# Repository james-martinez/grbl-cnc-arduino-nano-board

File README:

Made with Eagle 6.1

A milled board
[[gollum.png|frame|alt=Gollum and his precious wiki]]

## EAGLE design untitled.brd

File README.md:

A PCB layout and schematic.

Made with Eagle PCB 6.1

##Requirements
* an arduino nano w atmega328p loaded with grbl http://github.com/grbl/grbl
* at least 1 Pololu A4988 Stepper motor driver

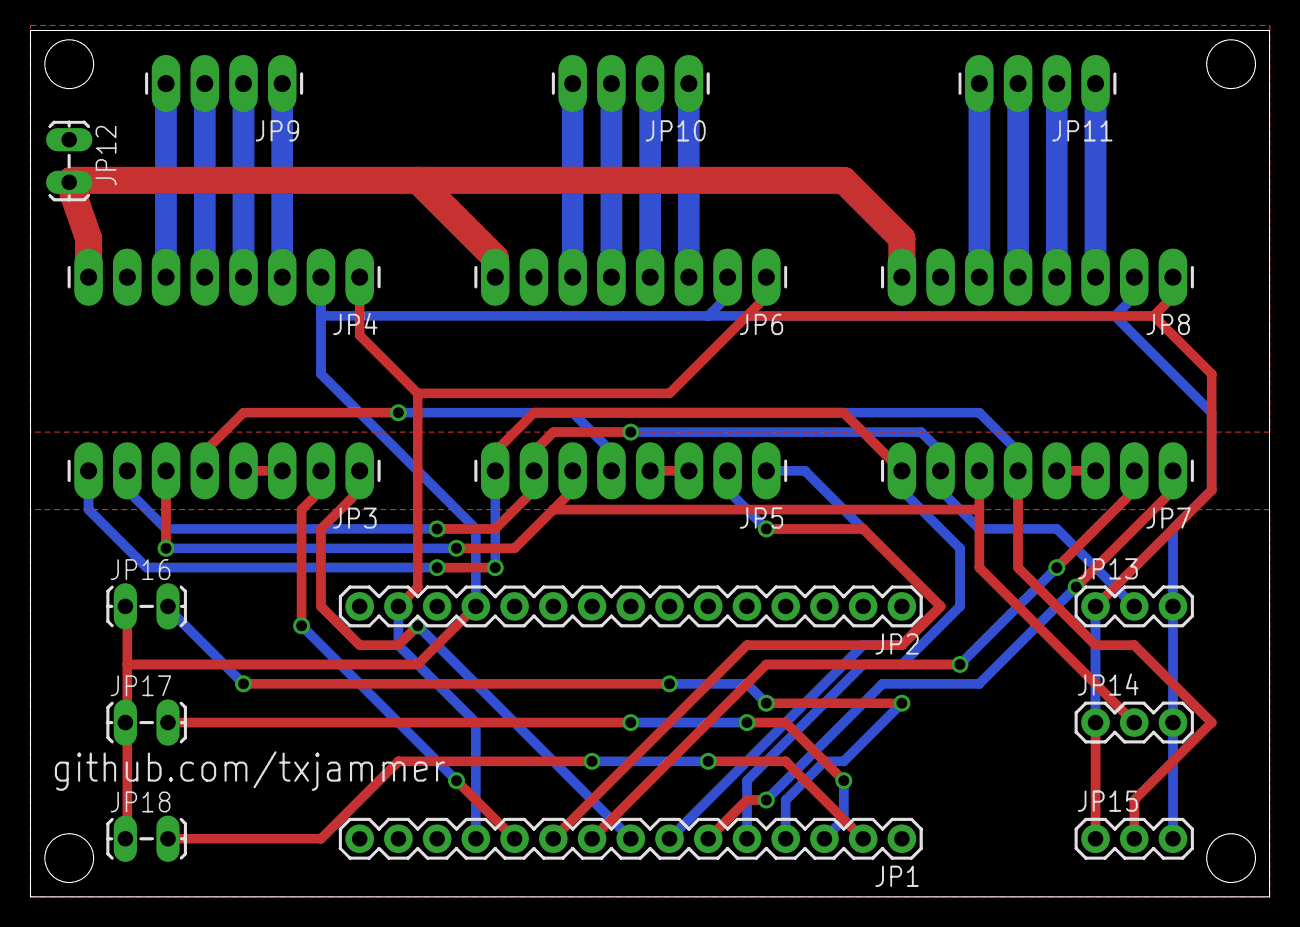
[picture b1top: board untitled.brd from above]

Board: 2 copper layers, 81.3 x 56.8 mm, 18 parts (0 on the bottom side), 32 nets.

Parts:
JP1, JP2: M15; 1X15
JP3, JP4, JP5, JP6, JP7, JP8: 1X08_LONGPADS
JP9, JP10, JP11: 1X04_LONGPADS
JP12, JP16, JP17, JP18: 1X02_LOCK_LONGPADS
JP13, JP14, JP15: 1X03

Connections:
5V: JP2.12, JP4.2, JP6.2, JP8.2, JP13.3, JP14.3, JP15.3, JP16.1, JP17.1, JP18.1
DISABLE: JP1.5, JP3.8, JP5.8, JP7.8
GND: JP1.12, JP2.14, JP4.1, JP6.1, JP8.1, JP13.1, JP14.1, JP15.1
GNDMOT: JP4.7, JP6.7, JP8.7, JP12.1
MS1: JP3.7, JP5.7, JP7.7, JP13.2
MS2: JP3.6, JP5.6, JP7.6, JP14.2
MS3: JP3.5, JP5.5, JP7.5, JP15.2
unnamed: JP5.3, JP5.4
unnamed: JP4.6, JP9.4
unnamed: JP4.5, JP9.3
unnamed: JP4.4, JP9.2
unnamed: JP4.3, JP9.1
unnamed: JP8.6, JP11.4
unnamed: JP8.5, JP11.3
unnamed: JP8.4, JP11.2
unnamed: JP8.3, JP11.1
unnamed: JP6.6, JP10.4
unnamed: JP6.5, JP10.3
unnamed: JP6.4, JP10.2
unnamed: JP6.3, JP10.1
unnamed: JP7.3, JP7.4
unnamed: JP3.3, JP3.4
VMOT: JP4.8, JP6.8, JP8.8, JP12.2
XDIR: JP1.8, JP3.1
XLIM: JP1.4, JP16.2
XSTP: JP1.11, JP3.2
YDIR: JP1.7, JP5.1
YLIM: JP1.3, JP17.2
YSTP: JP1.10, JP5.2
ZDIR: JP1.6, JP7.1
ZLIM: JP1.2, JP18.2
ZSTP: JP1.9, JP7.2

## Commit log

2012-02-09 added eagle files
2012-02-09 corrected spelling
2012-02-09 added gerbers and drills
2012-02-09 added drawings for lpkf router or self cnc dxf export.
2012-02-10 added ground planes
2012-02-13 connected sleep and rst, one was floating
2012-02-13 added gnd plane and rerouted
2012-02-14 left design files
2012-02-14 back to normal
2012-05-31 Add README
2012-05-31 Changed File name
2012-05-31 Added picture
2012-05-31 Replaced with other image
2012-11-21 replaced image
2014-10-15 Create License
2014-10-22 Rename License to LICENSE
